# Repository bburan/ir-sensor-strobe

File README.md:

# Strobed IR Emitter / Sensor Board

A small four‑channel infrared emitter/detector board. Four IR LEDs (OP140) are
driven as a single strobed array; four phototransistors (OP550) act as
independent detectors, each presenting an analog output to a downstream
acquisition system.

The strobe carrier can come from either an **on‑board ~500 Hz oscillator** or an
**external control signal**, selected by a jumper at J1. The optoelectronics
mount remotely and connect through headers. The board is all through‑hole and is
intended to be hand‑soldered.

---

## 1. Overview / Theory of Operation

The board contains three functional blocks that share a common +5 V / GND rail.

### 1.1 Strobed IR emitter (one switch, driving four LEDs)

```
 +5V ──┬─[68Ω R2]─▷|─ D1 ─┐
       ├─[68Ω R3]─▷|─ D2 ─┤
       ├─[68Ω R4]─▷|─ D3 ─┤   common cathode
       └─[68Ω R5]─▷|─ D4 ─┴────────────┐
                                        │ (collector)
   CTL ──┬─[1kΩ R1]── B  Q1 (2N4401)    ◄
         │                E ── GND
       [10kΩ R10]
         │
        GND
```

All four IR emitters (D1–D4, OP140) sit between the +5 V rail and a common node,
each with its own 68 Ω series resistor (R2–R5) setting the forward current to
roughly

```
I_LED ≈ (5 V − V_f − V_CE(sat)) / 68 Ω ≈ (5 − 1.5 − 0.2) / 68 ≈ 48 mA per LED
```

The common cathode node is pulled to ground by low‑side NPN switch **Q1**, driven
from the **CTL** node through the 1 kΩ base resistor **R1** (I_B ≈ 4.1 mA at 5 V).
When CTL is high, Q1 saturates and all four LEDs illuminate together; when CTL is
low the array is dark. Peak collector current in Q1 is the sum of the four
branches, **≈ 190 mA**.

R1 is deliberately left at 1 kΩ rather than a lower value. It has to be drivable
both by U1 and by an external source (see §1.2); dropping it to 470 Ω would gain
only ~5 % LED current while approaching the TLC555's ±10 mA output rating and
putting the external drive out of reach of a typical line‑level output.

The 10 kΩ resistor **R10** pulls CTL to ground so the array stays dark whenever
CTL is undriven or the J1 shunt is removed.

> **⚠ Q1 orientation differs between board revisions.** The current schematic
> uses an EBC pin mapping (pin 1 = emitter, pin 2 = base, pin 3 = collector),
> matching a standard TO‑92 2N4401 installed **per the silkscreen**.
>
> Boards fabricated from the *earlier* netlist have pads 1 and 3 transposed, and
> need Q1 inserted **rotated 180°** (flat face opposite the silkscreen). Built
> the other way round, Q1 runs reverse‑active (β_R ≈ 5–20 instead of ≈ 150) and
> the emitters run several times dim with nothing obviously wrong. See §6 for the
> one‑meter check that tells the two cases apart.

### 1.2 Strobe source — on‑board oscillator or external (J1)

```
                 +5V
                  │
                [1k R11]
                  │
    ┌─────────────┴── DIS (7)
    │                            ┌──────┐          J1
  [14k R12]      U1  TLC555 ─────┤ Q (3)├──── 1  ○ INT CTL
    │                            └──────┘         │
    ├─────────────┬── THR (6)                   2  ○ ── CTL ── R1 → Q1 base
    │             └── TR  (2)                      │
 [0.1µ C3]                                       3  ○ EXT CTL ── external drive
    │
   GND
```

**U1** is a TLC555 wired as a standard astable:

```
f = 1.44 / ((R11 + 2·R12) · C3) = 1.44 / ((1k + 28k) · 0.1 µF) ≈ 497 Hz
D = (R11 + R12) / (R11 + 2·R12) = 15k / 29k ≈ 51.7 %
```

C4 (0.01 µF) decouples the control‑voltage pin; C5 (0.1 µF) is local supply
bypass. RESET (pin 4) is tied to +5 V.

**J1 selects the strobe source** — the silkscreen marks the two ends **INT CTL**
and **EXT CTL**:

| Shunt | Source | Use |
|-------|--------|-----|
| **1–2** | On‑board oscillator (U1) | Board self‑strobes at ~497 Hz. No host output needed. |
| **2–3** | External drive | Host supplies the carrier on pin 3. |

With no shunt fitted, R10 holds CTL low and the array stays dark.

A CMOS TLC555 is specified rather than a bipolar NE555 deliberately: its output
swings close to the rails (a bipolar 555 drops ~1.7 V, starving Q1's base) and it
does not inject the large supply transients an NE555 does on each edge, which
matters on a board carrying 10 kΩ‑impedance analog sensor lines.

**Why ~50 % duty.** For a square carrier of fixed peak current, the amplitude
recovered at the fundamental is (2·I_pk/π)·sin(πD), maximised at D = 0.5. The
maximum is flat, so the astable's 51.7 % costs about 0.15 % — the diode trick
often used to force exactly 50 % is unnecessary here.

### 1.3 Photodetectors (four independent channels)

```
 +5V ──[10kΩ]──┬──────► Vout (to J2 / J6)
               │ C
              (Q_photo, OP550)
               │ E
              GND (J5)
```

Each phototransistor (Q2–Q5, OP550) is wired common‑emitter: collector pulled to
+5 V through a 10 kΩ load resistor (R6–R9), emitter to ground. The output is
taken at the collector:

* **Dark / no IR:** phototransistor off → output pulled high (≈ +5 V).
* **Illuminated:** phototransistor conducts → output pulled toward ground.

The response is therefore **inverting**. The four channels are electrically
independent; only the emitter array is strobed, in common.

The detectors are *not* modulated — only the emitters are. Recovering the signal
at the carrier frequency (e.g. quadrature demodulation at ~497 Hz) rejects
ambient light, mains‑derived flicker, and the DC offset of each phototransistor,
which is what makes the board usable through an AC‑coupled input.

### 1.4 Notes and caveats

* **Supply bypassing is on‑board.** C1 (10 µF) + C2 (0.1 µF) sit across the
  +5 V/GND entry at J4 to absorb the ~190 mA switching transient of the emitter
  array. Additional bulk upstream never hurts on a long supply lead.
* **CTL has an on‑board pulldown.** R10 (10 kΩ) holds CTL low when undriven or
  unjumpered, so the array defaults to dark. Any 3.3–5 V logic high will switch
  Q1.
* **The emitters cannot be gated individually.** One switch drives all four. The
  detectors are read individually.
* **No reverse‑polarity or over‑current protection.** Observe supply polarity at
  J4 — C1 is polarized and a reversed supply will stress it along with Q1 and the
  phototransistors.

---

## 2. Bill of Materials (what to order)

Quantities are per board. All parts are through‑hole. 27 placements, 75 joints.

| Ref(s)            | Qty | Value / Part     | Package / Footprint                          | Notes |
|-------------------|-----|------------------|----------------------------------------------|-------|
| R1, R11           | 2   | 1 kΩ             | Axial ¼ W, 7.62 mm pitch (DIN0207)           | Q1 base resistor; 555 charge resistor |
| R2, R3, R4, R5    | 4   | 68 Ω             | Axial ¼ W, 7.62 mm pitch                     | LED ballast, ~48 mA each (82 mW worst case) |
| R6, R7, R8, R9    | 4   | 10 kΩ            | Axial ¼ W, 7.62 mm pitch                     | Phototransistor collector load |
| R10               | 1   | 10 kΩ            | Axial ¼ W, 7.62 mm pitch                     | CTL pulldown |
| R12               | 1   | 14 kΩ            | Axial ¼ W, 7.62 mm pitch                     | 555 timing (E96 value) |
| C1                | 1   | 10 µF            | Radial electrolytic, 2.5 mm pitch (polarized)| Bulk bypass at J4; observe polarity |
| C2, C3, C5        | 3   | 0.1 µF           | Ceramic disc, 2.5 mm pitch                   | C2 supply HF bypass, C3 555 timing, C5 U1 local bypass |
| C4                | 1   | 0.01 µF          | Ceramic disc, 2.5 mm pitch                   | 555 control‑voltage decoupling |
| U1                | 1   | TLC555CP         | DIP‑8, 7.62 mm row spacing                   | **CMOS** 555 — do not substitute NE555 (see §1.2) |
| Q1                | 1   | 2N4401           | TO‑92 (inline)                               | EBC pinout. **See orientation warning in §1.1** |
| J1                | 1   | 3‑pin header     | 2.54 mm PinHeader 1×03                       | Strobe source select (INT CTL / EXT CTL) |
| J2                | 1   | 4‑pin header     | 2.54 mm PinHeader 1×04                       | Detector outputs to acquisition |
| J3                | 1   | 5‑pin header     | 2.54 mm PinHeader 1×05                       | Ground bus for the Vout harness |
| J4                | 1   | 2‑pin header     | 2.54 mm PinHeader 1×02                       | Power in: pin 1 = +5 V, pin 2 = GND |
| J5                | 1   | 4‑pin header     | 2.54 mm PinHeader 1×04                       | OP550 return (emitters, all GND) |
| J6                | 1   | 4‑pin header     | 2.54 mm PinHeader 1×04                       | OP550 out (collectors) |
| J7                | 1   | 4‑pin header     | 2.54 mm PinHeader 1×04                       | OP140 in (common cathode return) |
| J8                | 1   | 4‑pin header     | 2.54 mm PinHeader 1×04                       | OP140 out (anodes) |

**Off‑board optoelectronics** (not on the PCB, wired via the harness — see §3.2):

| Ref(s)          | Qty | Part                  | Notes |
|-----------------|-----|-----------------------|-------|
| D1, D2, D3, D4  | 4   | OP140 IR emitter      | Anode to J8, cathode to J7 |
| Q2, Q3, Q4, Q5  | 4   | OP550 phototransistor | Collector to J6, emitter to J5 |

**Emitter/detector wavelength.** Confirm the detector's spectral response
overlaps the emitter's output for your specific parts before ordering in
quantity, and consult current datasheets for lead configuration.

**Sourcing note.** Through‑hole ICs are being discontinued industry‑wide. If
TLC555CP (DIP‑8) becomes hard to source, the SOIC‑8 TLC555CD is cheaper and
better stocked, but requires a footprint change.

---

## 3. Assembly

All through‑hole, hand‑solder friendly. Nothing requires reflow. Budget roughly
20–30 minutes per board.

### 3.1 Soldering order

Populate lowest‑profile parts first so the board sits flat while you work:

1. **Resistors R1–R12** (axial). Bend leads to the 7.62 mm pitch, seat flat,
   solder, trim. Non‑polar. Double‑check value groups:
   * R1, R11 = 1 kΩ
   * R2–R5 = 68 Ω (LED ballast)
   * R6–R9 = 10 kΩ (detector load)
   * R10 = 10 kΩ (CTL pulldown)
   * R12 = 14 kΩ (555 timing) — easy to confuse with the 10 kΩ group
2. **Ceramic caps C2, C3, C4, C5** (non‑polar) and **transistor Q1** (TO‑92).
   **Check §1.1 for Q1's orientation before soldering — it depends on which board
   revision you have.** Seat Q1 with a few mm of lead so the case is not stressed.
3. **U1** (DIP‑8). Match pin 1 to the notch/dot on the silkscreen. A socket is
   worth fitting if you expect to experiment with the timing components.
4. **Headers J1–J8.** Solder one pin, reflow while pressing the header flush and
   square, then solder the rest. Pin 1 of each connector is the
   **square/rectangular pad**.
5. **Electrolytic cap C1** (10 µF, **polarized**). Match the `+` lead to the `+`
   pad; the silkscreen band indicates the negative side.

Clean flux as appropriate and inspect for bridges, especially at the connector
rows.

### 3.2 Remote optoelectronics harness

The OP140 emitters and OP550 detectors are **not** mounted on the PCB. They are
wired on flying leads so they can be positioned on a fixture — aimed across a
nose‑poke or lick spout, for example. Four headers carry them:

| Header | Silk | Carries | Pin mapping |
|--------|------|---------|-------------|
| **J8** | OP140 | LED **anodes** (one per channel, each via its own ballast) | pin 1 → D4, pin 2 → D3, pin 3 → D2, **pin 4 → D1** |
| **J7** | OP140 | LED **cathodes** — all four pins common, returning to Q1 | any pin; one per LED keeps the harness symmetric |
| **J6** | OP550 | Detector **collectors** (the outputs) | pin 1 → Q2, pin 2 → Q3, pin 3 → Q4, pin 4 → Q5 |
| **J5** | OP550 | Detector **emitters** — all four pins are GND | one per detector, giving each channel its own return |

> **⚠ J8's pin order is reversed** relative to the D1–D4 reference designators
> (pin 1 is D4, pin 4 is D1). J6 runs in order (pin 1 = Q2 … pin 4 = Q5). Check
> this when building the harness; getting it backwards silently swaps which
> physical emitter pairs with which detector channel.

Polarity out at the remote device still matters: the OP140 anode goes to J8 and
its cathode to J7; the OP550 collector goes to J6 and its emitter to J5. A
reversed LED will not emit; a reversed phototransistor will not conduct properly.

Giving each detector its own return conductor to J5 rather than daisy‑chaining
them keeps inter‑channel ground coupling down on long harnesses.

---

## 4. PCB Fabrication (what to order)

Generate Gerbers/drill from `IR sensor strobe.kicad_pcb` (KiCad 8:
*File → Fabrication Outputs → Gerbers* and *Drill Files*), or order directly from
the KiCad project at any standard fab.

| Parameter        | Value                                  |
|------------------|----------------------------------------|
| Layers           | 2 (F.Cu / B.Cu)                        |
| Board size       | ≈ 37.5 mm × 43.5 mm                    |
| Thickness        | 1.6 mm                                 |
| Material         | FR‑4                                   |
| Finish           | HASL or ENIG (either is fine — all THT)|
| Min feature      | Default KiCad clearances; no fine‑pitch parts, so any vendor's economy process is adequate |
| Silkscreen       | Both sides used (title/attribution on back) |

There are no controlled‑impedance, high‑voltage, or thermal requirements.

The back silkscreen reads *"Strobed IR emitter/sensor w/ internal generator"*,
which distinguishes this revision from the earlier board — worth checking before
assembly, since Q1's orientation differs between the two (§1.1).

**If ordering assembled:** the board is 100 % through‑hole, which is the
worst‑priced category at every CM because it is hand‑soldered. At low quantity
hand assembly is usually cheaper than the setup fees. If assembly cost matters at
volume, converting the passives to 0805 and U1 to SOIC‑8 moves the bulk of the
work onto automated SMT and leaves only the nine connectors to solder by hand.

---

## 5. Connector Pinout & Usage

| Connector | Pins | Signal | Direction | Description |
|-----------|------|--------|-----------|-------------|
| **J4** (Power) | 1 | +5 V | in | Board supply. |
|                | 2 | GND  | in | Supply return. |
| **J1** (CTL select) | 1 | INT CTL | — | On‑board oscillator output (U1 pin 3). |
|                     | 2 | CTL     | — | Q1 base drive. Shunt 1–2 for internal, 2–3 for external. |
|                     | 3 | EXT CTL | in | External strobe input. Logic high → all IR LEDs on. |
| **J2** (Vout)  | 1–4 | Vout[1..4] | out | The four detector outputs, same nets as J6. High ≈ dark, low ≈ illuminated. |
| **J3** (GND)   | 1–5 | GND | — | Ground bus; all five pins common. Return/reference for the Vout harness. |
| **J5** (OP550 return) | 1–4 | GND | — | Detector emitter returns. |
| **J6** (OP550 out)    | 1–4 | Vout[1..4] | — | Detector collectors — the remote sensor cable. |
| **J7** (OP140 in)     | 1–4 | LED common cathode | — | All four pins common, returning to Q1's collector. |
| **J8** (OP140 out)    | 1–4 | LED anodes | — | One per channel, **reverse order** — see §3.2. |

J2 and J6 are the same four nets: J6 faces the remote sensor harness, J2 faces
the acquisition system. That is deliberate fan‑out, not a duplicate.

### Typical connection

1. Supply **+5 V / GND** to **J4** (on‑board bypass C1/C2 handles local
   decoupling — see §1.4).
2. Fit the **J1** shunt: **1–2** to let the board strobe itself at ~497 Hz, or
   **2–3** and drive **EXT CTL** from a host timer/GPIO.
3. Wire the remote optoelectronics to **J5–J8** per §3.2.
4. Read the four **J2 (Vout)** channels on the host, referenced to a **J3**
   ground, and demodulate at the carrier frequency.

---

## 6. Bring‑up / Test

1. **Unpowered:** verify J4 polarity. A resistance check from +5 V to GND will
   briefly show C1/C2 charging before settling high — it should **not** read a
   hard short. Confirm C1's polarity.
2. **Power, no J1 shunt:** apply +5 V. R10 holds CTL low, so the array is dark.
   Each Vout on J2 should read ≈ +5 V (detectors dark, pulled up through 10 kΩ).
   Quiescent current is small.
3. **Oscillator:** fit the J1 shunt on **1–2** and scope U1 pin 3. Expect a
   roughly square wave near **497 Hz at ~52 % duty**, swinging close to the
   rails. If it sits stuck at either rail, check RESET (pin 4) is at +5 V and
   that R12 is the 14 kΩ part, not a stray 10 kΩ.
4. **Emitter current — the Q1 orientation check.** With the strobe running,
   measure the DC voltage across any one 68 Ω ballast (R2–R5):
   * **≈ 1.6 V** (≈ 24 mA average at 50 % duty) → Q1 is correctly oriented.
   * **Well under 0.5 V** → Q1 is reverse‑active. Re‑read §1.1 and flip it.

   Confirm IR emission with a phone camera (a faint pale/purple glow on many
   sensors) or an IR‑sensitive card.
5. **Detector response:** with the emitters running, illuminate a detector
   (reflect off a nearby surface, or point an IR source at it). Its Vout should
   show the carrier, and the amplitude should collapse when the beam is blocked.
   Repeat per channel.
6. **End to end:** demodulate each channel at the carrier frequency and confirm
   that breaking the beam produces a large, unambiguous amplitude drop.

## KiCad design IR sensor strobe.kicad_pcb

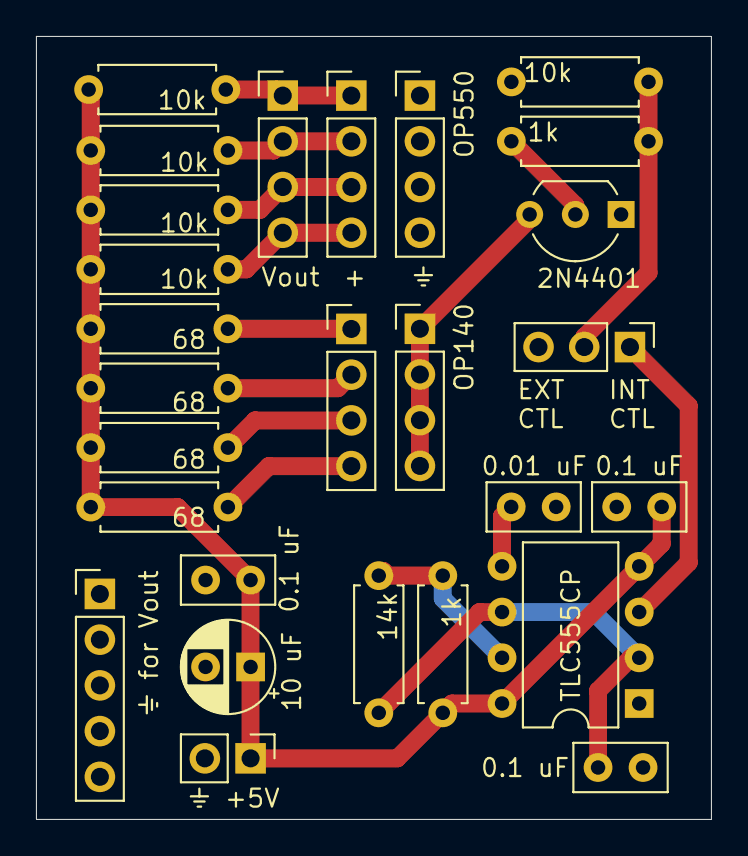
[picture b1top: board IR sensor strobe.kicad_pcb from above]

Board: 2 copper layers, 37.5 x 43.5 mm, 27 parts (0 on the bottom side), 17 nets.

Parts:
C1: 10 uF; CP_Radial_D5.0mm_P2.50mm
C2, C3, C5: 0.1 uF; C_Disc_D5.0mm_W2.5mm_P2.50mm
C4: 0.01 uF; C_Disc_D5.0mm_W2.5mm_P2.50mm
J1: CTL select; PinHeader_1x03_P2.54mm_Vertical
J2: Sensors; PinHeader_1x04_P2.54mm_Vertical
J3: Conn_01x05; PinHeader_1x05_P2.54mm_Vertical
J4: Conn_01x02; PinHeader_1x02_P2.54mm_Vertical
J5: OP550 return; PinHeader_1x04_P2.54mm_Vertical
J6: OP550 out; PinHeader_1x04_P2.54mm_Vertical
J7: OP140 in; PinHeader_1x04_P2.54mm_Vertical
J8: OP140 out; PinHeader_1x04_P2.54mm_Vertical
Q1: 2N4401; TO-92_Inline_Wide
R1, R11: 1k; R_Axial_DIN0207_L6.3mm_D2.5mm_P7.62mm_Horizontal
R2, R3, R4, R5: 68; R_Axial_DIN0207_L6.3mm_D2.5mm_P7.62mm_Horizontal
R6, R7, R8, R9, R10: 10k; R_Axial_DIN0207_L6.3mm_D2.5mm_P7.62mm_Horizontal
R12: 14k; R_Axial_DIN0207_L6.3mm_D2.5mm_P7.62mm_Horizontal
U1: TLC555CP; DIP-8_W7.62mm

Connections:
+5V: C1.1, C2.1, C5.1, J4.1, R2.1, R3.1, R4.1, R5.1, R6.1, R7.1, R8.1, R9.1, R11.1, U1.4 (R), U1.8 (VCC)
/OSC: J1.1, U1.3 (Q)
GND: C1.2, C2.2, C3.2, C4.2, C5.2, J3.1, J3.2, J3.3, J3.4, J3.5, J4.2, J5.1, J5.2, J5.3, J5.4, Q1.1 (E), R10.2, U1.1 (GND)
unnamed: J1.2, R1.2, R10.1
unnamed: J2.1, J6.1, R6.2
unnamed: J2.2, J6.2, R7.2
unnamed: J2.3, J6.3, R8.2
unnamed: J2.4, J6.4, R9.2
unnamed: J7.1, J7.2, J7.3, J7.4, Q1.3 (C)
unnamed: J8.1, R5.2
unnamed: J8.2, R4.2
unnamed: J8.3, R3.2
unnamed: J8.4, R2.2
unnamed: Q1.2 (B), R1.1
unnamed: C4.1, U1.5 (CV)
unnamed: R11.2, R12.1, U1.7 (DIS)
unnamed: C3.1, R12.2, U1.2 (TR), U1.6 (THR)
